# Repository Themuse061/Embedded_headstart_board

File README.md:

# Embedded_headstart_board

## How to use

> [!NOTE]
> Dear trainees, please note that this is the first version of this guide and it may contain errors. If you spot anything or something isn't working as expected, please contact [me](https://github.com/Fiedal) (if it comes to this readme or software) or [owner of this repo](https://github.com/Themuse061) (if it comes to hardware).

### Schematics

First of all, you are going to need software that allows you to read the schematics of the board. That's one of the most important skills for an embedded programmer. My main recommendation is installing **KiCad**, the EDA software in which this board was created. Another great alternative is [KiCanvas](https://kicanvas.org/), an online viewer for KiCad PCB layouts and schematics. It works great for simpler boards like this one, though KiCad is better for more complex projects.

### Altmode and Chainbus mode

MMS3 (the main board that this PCB connects to) has two modes: **Altmode** and **Chainbus mode**. What's the difference?

- **Chainbus mode:** This is the default mode. It lets you stack multiple hats (boards like this one) onto the MMS3 to build a tower (up to 8 boards). The tradeoff is that you only have SPI, I2C, and UART available on each hat. This means you cannot use direct hardware interrupts on peripherals located on the hat. However, you can still control simple peripherals using a GPIO expander. More details will be available in the upcoming MODUCAR and MMS3 documentation.

- **Altmode:** This mode is designed for specific use cases (like this headstart board). In Altmode, only a single hat can be connected to the MMS3, but you get access to a whole row of dedicated pins alongside the standard Chainbus interface. You can configure these free pins however you like: direct interrupts, SPI, USART, or ADC! Check the main schematic of this board to see the table showing how each pin can be assigned in Altmode.

*Note:* On this specific board, you don't need to manually switch modes – it was designed specifically to work in **Altmode**.

### Programming

There are several ways to program STM32 microcontrollers: using STM's official HAL (Hardware Abstraction Layer), writing bare-metal code, or using third-party libraries and OSes.

In KoNaR, we primarily use two approaches:
- [StmEpic](https://github.X-Lemon-X/StmEpic) – A library developed within KoNaR (used in Nomad) that acts as an abstraction layer over HAL, integrated with FreeRTOS.
- [Zephyr RTOS](https://docs.zephyrproject.org/latest/index.html) – An RTOS ecosystem used in Hefajstos (and currently being prepared for Nomad). Unlike lightweight RTOSes, Zephyr is a full ecosystem supporting multiple architectures, built-in connectivity stacks, Devicetree hardware description, and Kconfig build control.

We recommend starting with **HAL** first, as it is beginner-friendly and helps you understand what happens under the hood before moving to StmEpic or Zephyr.

#### HAL
Clone this [template repository](https://github.com/Fiedal/MMS-embedded-headstart-software-base). It already includes the base Chainbus pin definitions. All you need to do is configure the Altmode pins inside STM32CubeMX (`.ioc` file), generate the project code, and flash the board.

#### StmEpic
**TODO**

#### Zephyr
A template for Zephyr RTOS is currently under development. In the meantime, check out this [Zephyr tutorial video](https://www.youtube.com/watch?v=mTJ_vKlMS_4) and refer to the official [Zephyr Documentation](https://docs.zephyrproject.org/latest/index.html). You can also look at the existing [mms_board_definitions repository](https://github.com/KoNaR-Hefajstos/mms_board_definitions).

---

### Dictionary
- **uC / MCU:** Microcontroller Unit
- **GPIO:** General-Purpose Input/Output
- **Blinky:** A simple LED toggling program (the "Hello World" of embedded systems)
- **Debouncing:** Mechanical buttons bounce back and forth rapidly when pressed, causing false triggers. Debouncing (in hardware or software) filters out these quick oscillations to register only a single clean press.

---

### Project Ideas

Here are a few project suggestions to help you combine different hardware peripherals on the board. Try bringing up each peripheral individually first before building a full project!

- **Smart Blinky:** Use direct GPIOs to build a status blinky with multiple modes (e.g., fast blink, heartbeat pattern, slow blink). Change modes using a tactile button configured with external interrupts. *Watch out for button debouncing in your interrupt handler!*

- **Home Temperature & Humidity Station:** Read data from the DHT11 sensor and display the temperature or humidity on the 7-segment display. Use a push button to toggle between showing temperature and humidity.

- **Digital Spirit Level / Tilt Sensor:** Use the onboard sensor MPU-6500 to detect tilt. Display the current angle on the 7-segment display or light up specific LEDs on the board depending on whether it's tilted left or right.

- **Simon Says Game:** Use the GPIO Expander section to create a Simon Says memory game. The LEDs blink in a random sequence, and the user must repeat the sequence using the buttons. Add difficulty scaling with faster blinks or longer sequences!

> [!NOTE]
> If you're building one of these projects using HAL, try integrating FreeRTOS to get familiar with multi-tasking concepts. It's not mandatory right away, but understanding RTOS fundamentals will be essential for future KoNaR projects!

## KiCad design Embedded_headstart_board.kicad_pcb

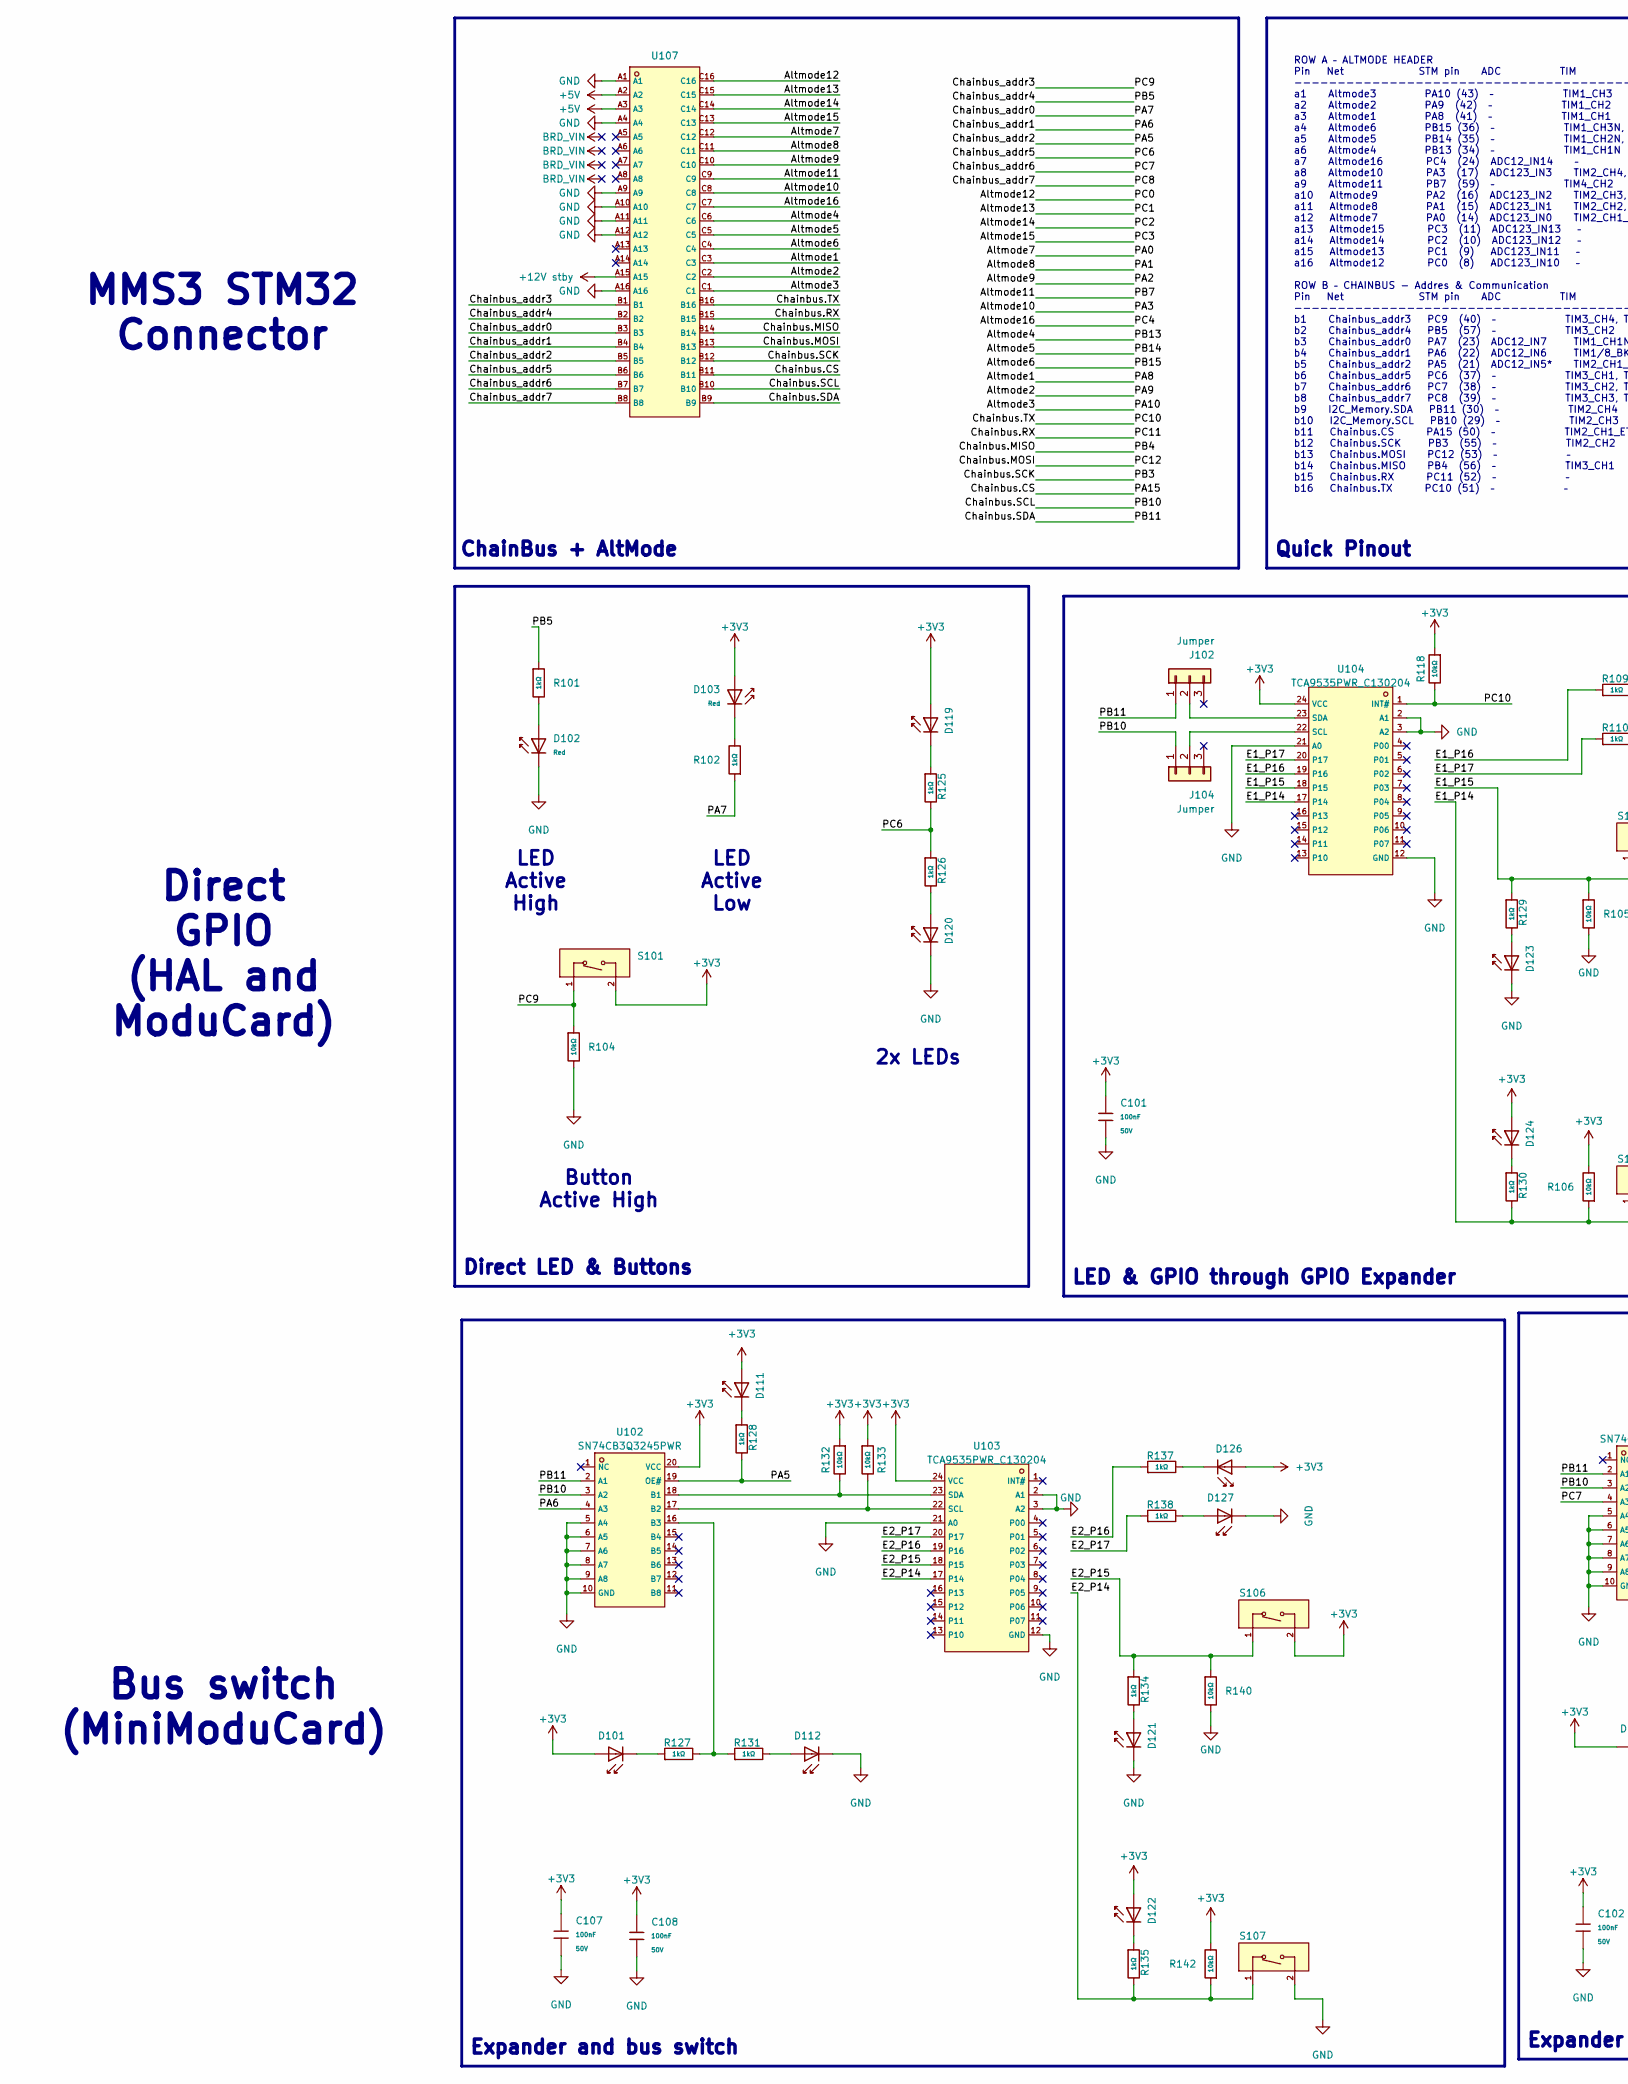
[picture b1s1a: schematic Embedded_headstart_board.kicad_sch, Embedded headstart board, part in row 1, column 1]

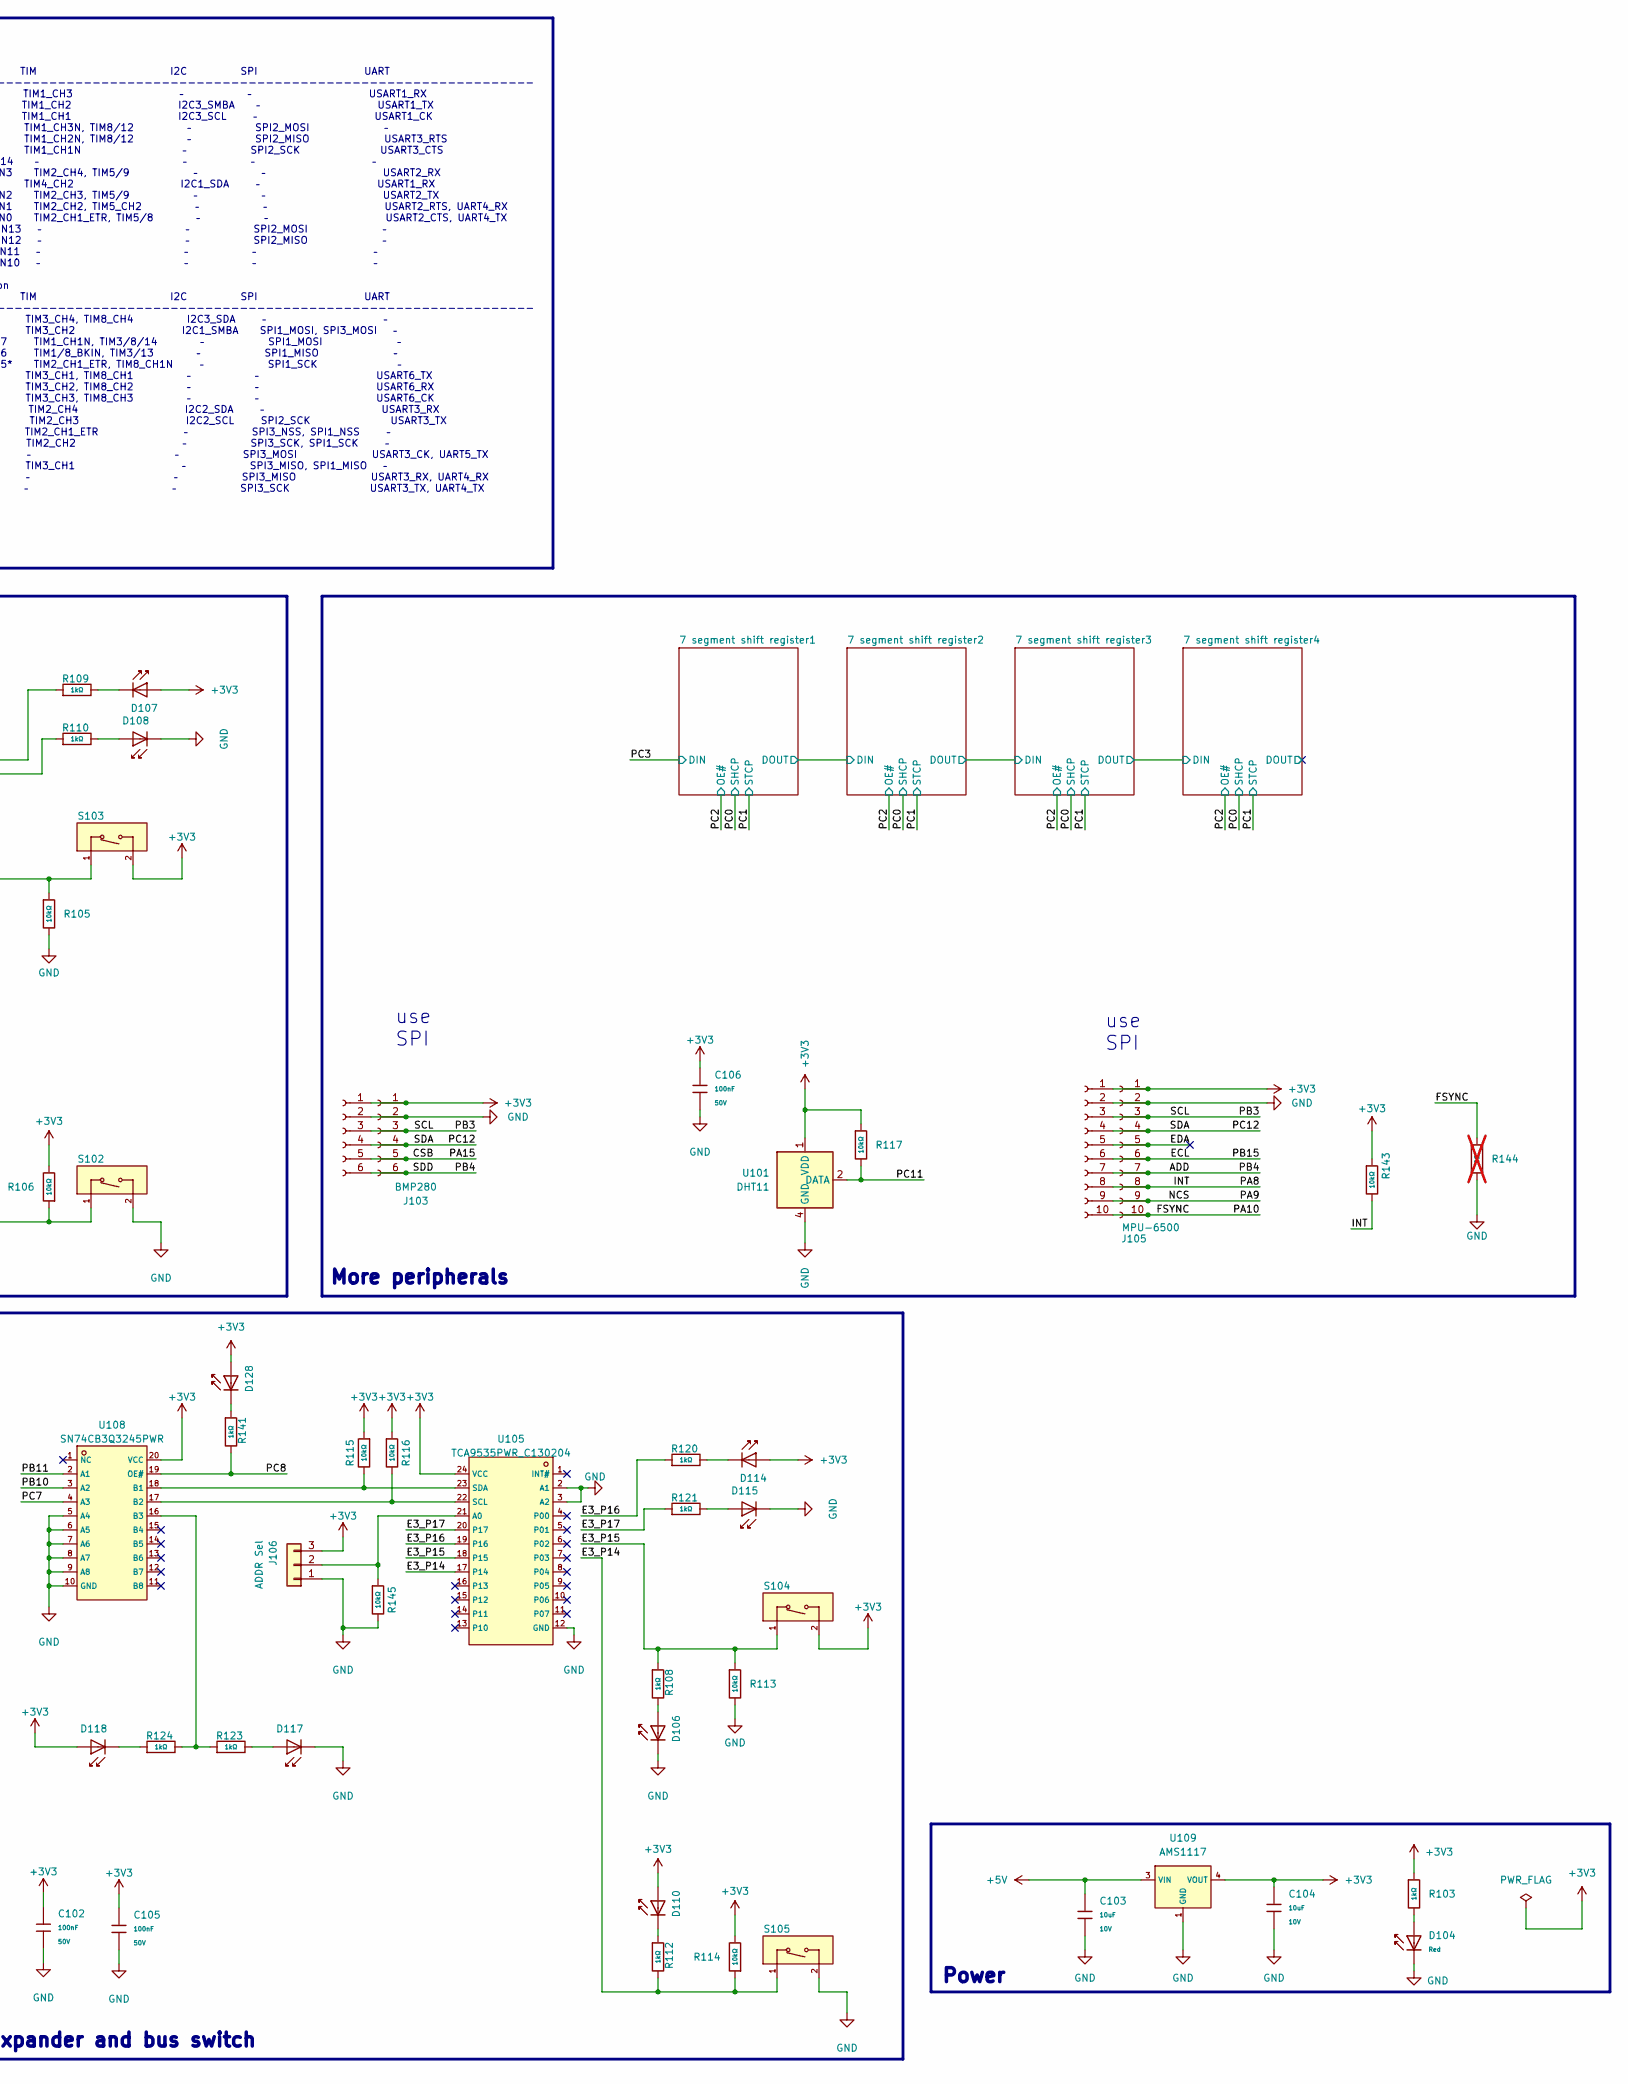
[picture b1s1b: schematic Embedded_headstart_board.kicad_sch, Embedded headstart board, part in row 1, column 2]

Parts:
C101, C102, C105, C106, C107, C108: 100nF; C_0603; Voltage Rated 50V; Tolerance ±10%; Part CC0603KRX7R9BB104; LCSC C14663
C103, C104: 10uF; C_0603; Voltage Rated 10V; Tolerance ±10%; Part CL10A106KP8NNNC; LCSC C19702
D101, D102, D103, D104, D107, D108, D111, D112, D114, D115, D117, D118, D119, D120, D126, D127, D128: Red; Multi_diode; Part KT-0603R; LCSC C2286
D106, D110, D121, D122, D123, D124: Red; D_0603; Part KT-0603R; LCSC C2286
J102, J104: Jumper; PinHeader_1x03_P2.54mm_Vertical
J103, J107: BMP280; PinHeader_1x06_P2.54mm_Vertical
J105, J108: MPU-6500; PinHeader_1x10_P2.54mm_Vertical
J106: ADDR Sel; PinHeader_1x03_P2.54mm_Vertical
R101, R102, R103, R108, R109, R110, R112, R120, R121, R123, R124, R125, R126, R127, R128, R129, R130, R131, R134, R135, R137, R138, R141: 1kΩ; R_0603; Overload Voltage (Max) 75V; Tolerance ±1%; Part 0603WAF1001T5E; LCSC C21190
R104, R105, R106, R113, R114, R115, R116, R117, R118, R132, R133, R140, R142, R143, R145: 10kΩ; R_0603; Overload Voltage (Max) 75V; Tolerance ±1%; Part 0603WAF1002T5E; LCSC C25804
R144: 0Ω; R_0603; Overload Voltage (Max) 75V; Tolerance ±1%; Part 0603WAF0000T5E; LCSC C21189; not fitted
S101, S102, S103, S104, S105, S106, S107: Tactile Button, 160gf; MultiSwitch; LCSC C55014078
U101: DHT11; Aosong_DHT11_5.5x12.0_P2.54mm
U102, U108: SN74CB3Q3245PWR; C470961_TSSOP-20_L6_5-W4_4-P0_65-LS6_4-BL; LCSC C470961
U103, U104, U105: TCA9535PWR_C130204; C130204_TSSOP-24_L7_8-W4_4-P0_65-LS6_4-BL; LCSC C22396388
U107: 9001-17481C00A_C5173377; C5173377_CONN-TH_9001-17481C00A; LCSC C5173377
U109: AMS1117; SOT-223-3_L6.5-W3.4-P2.30-LS7.0-BR; Output Voltage 3.3V; Dropout Voltage 1.3V@(800mA); Part AMS1117-3.3; LCSC C6186

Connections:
+3V3: C101.1, C102.1, C104.1, C105.1, C106.1, C107.1, C108.1, D101.2, D103.2, D107.2, D110.2, D111.2, D114.2, D118.2, D119.2, D122.2, D124.2, D126.2, D128.2, J103.1, J105.1, J106.3, J107.1, J108.1, R103.1, R106.2, R114.2, R115.1, R116.1, R117.1, R118.1, R132.1, R133.1, R142.2, R143.1, S101.2 (B), S103.2 (B), S104.2 (B), S106.2 (B), U101.1 (VDD), U102.20 (VCC), U103.24 (VCC), U104.24 (VCC), U105.24 (VCC), U108.20 (VCC), U109.2 (VOUT), U109.4 (VOUT); also elsewhere on the board
+5V: C103.1, U107.A2, U107.A3, U109.3 (VIN)
+12V stby: U107.A15
/ADD: J103.6, J105.7, J107.6, J108.7, U107.B14
/Altmode1: J105.8, J108.8, R143.2, U107.C3
/Altmode2: J105.9, J108.9, U107.C2
/Altmode3: J105.10, J108.10, R144.1, U107.C1
/Altmode4: U107.C6
/Altmode5: U107.C5
/Altmode6: J105.6, J108.6, U107.C4
/Altmode7: U107.C12
/Altmode8: U107.C11
/Altmode9: U107.C10
/Altmode10: U107.C8
/Altmode11: U107.C9
/Altmode12: U107.C16; also elsewhere on the board
/Altmode13: U107.C15; also elsewhere on the board
/Altmode14: U107.C14; also elsewhere on the board
/Altmode15: U107.C13; also elsewhere on the board
/Altmode16: U107.C7
/CSB: J103.5, J107.5, U107.B11
/Chainbus.MOSI: J103.4, J105.4, J107.4, J108.4, U107.B13
/Chainbus.RX: R117.2, U101.2 (DATA), U107.B15
/Chainbus.SCK: J103.3, J105.3, J107.3, J108.3, U107.B12
/Chainbus.SCL: J104.1, U102.3 (A2), U107.B10, U108.3 (A2)
/Chainbus.SDA: J102.1, U102.2 (A1), U107.B9, U108.2 (A1)
/Chainbus.TX: R118.2, U104.1 (INT#), U107.B16
/Chainbus_addr0: R102.1, U107.B3
/Chainbus_addr1: U102.4 (A3), U107.B4
/Chainbus_addr2: R128.2, U102.19 (OE#), U107.B5
/Chainbus_addr3: R104.1, S101.1 (A), U107.B1
/Chainbus_addr4: R101.1, U107.B2
/Chainbus_addr5: R125.2, R126.1, U107.B6
/Chainbus_addr6: U107.B7, U108.4 (A3)
/Chainbus_addr7: R141.2, U107.B8, U108.19 (OE#)
/E1_P14: R106.1, R130.2, S102.1 (A), U104.17 (P14)
/E1_P15: R105.1, R129.1, S103.1 (A), U104.18 (P15)
/E1_P16: R109.1, U104.19 (P16)
/E1_P17: R110.1, U104.20 (P17)
/E2_P14: R135.2, R142.1, S107.1 (A), U103.17 (P14)
/E2_P15: R134.1, R140.1, S106.1 (A), U103.18 (P15)
/E2_P16: R137.1, U103.19 (P16)
/E2_P17: R138.1, U103.20 (P17)
/E3_P14: R112.2, R114.1, S105.1 (A), U105.17 (P14)
/E3_P15: R108.1, R113.1, S104.1 (A), U105.18 (P15)
/E3_P16: R120.1, U105.19 (P16)
/E3_P17: R121.1, U105.20 (P17)
/EDA: J105.5, J108.5
GND: C101.2, C102.2, C103.2, C104.2, C105.2, C106.2, C107.2, C108.2, D102.1, D104.1, D106.1, D108.1, D112.1, D115.1, D117.1, D120.1, D121.1, D123.1, D127.1, J103.2, J105.2, J106.1, J107.2, J108.2, R104.2, R105.2, R113.2, R140.2, R144.2, R145.2, S102.2 (B), S105.2 (B), S107.2 (B), U101.4 (GND), U102.5 (A4), U102.6 (A5), U102.7 (A6), U102.8 (A7), U102.9 (A8), U102.10 (GND), U103.2 (A1), U103.3 (A2), U103.12 (GND), U103.21 (A0), U104.2 (A1), U104.3 (A2), U104.12 (GND), U104.21 (A0), U105.2 (A1), U105.3 (A2), U105.12 (GND), U107.A1, U107.A4, U107.A9, U107.A10, U107.A11, U107.A12, U107.A16, U108.5 (A4), U108.6 (A5), U108.7 (A6), U108.8 (A7), U108.9 (A8), U108.10 (GND), U109.1 (GND); also elsewhere on the board
unnamed: D101.1, R127.1
unnamed: D102.2, R101.2
unnamed: D103.1, R102.2
unnamed: D104.2, R103.2
unnamed: D106.2, R108.2
unnamed: D107.1, R109.2
unnamed: D108.2, R110.2
unnamed: D110.1, R112.1
unnamed: D111.1, R128.1
unnamed: D112.2, R131.2
unnamed: D114.1, R120.2
unnamed: D115.2, R121.2
unnamed: D117.2, R123.2
unnamed: D118.1, R124.1
unnamed: D119.1, R125.1
unnamed: D120.2, R126.2
unnamed: D121.2, R134.2
unnamed: D122.1, R135.1
unnamed: D123.2, R129.2
unnamed: D124.1, R130.1
unnamed: D126.1, R137.2
unnamed: D127.2, R138.2
unnamed: D128.1, R141.1
unnamed: J102.2, U104.23 (SDA)
unnamed: J104.2, U104.22 (SCL)
unnamed: J106.2, R145.1, U105.21 (A0)
unnamed: R132.2, U102.18 (B1), U103.23 (SDA)
unnamed: R133.2, U102.17 (B2), U103.22 (SCL)
unnamed: R127.2, R131.1, U102.16 (B3)
unnamed: R116.2, U105.22 (SCL), U108.17 (B2)
unnamed: R115.2, U105.23 (SDA), U108.18 (B1)
unnamed: R123.1, R124.2, U108.16 (B3)

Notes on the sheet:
use SPI
LED Active Low
Power
LED & GPIO through GPIO Expander
Direct GPIO (HAL and ModuCard)
2x LEDs
LED Active High
Direct LED & Buttons
Button Active High
ChainBus + AltMode
ROW A – ALTMODE HEADER Pin Net STM pin ADC TIM I2C SPI UART ------------------------------------------------------------------------------------------ a1 Altmode3 PA10 (43) – TIM1_CH3 – – USART1_RX a2 Altmode2 PA9 (42) – TIM1_CH2 I2C3_SMBA – USART1_TX a3 Altmode1 PA8 (41) – TIM1_CH1 I2C3_SCL – USAR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
Expander and bus switch
Quick Pinout
More peripherals
Bus switch (MiniModuCard)
MMS3 STM32 Connector

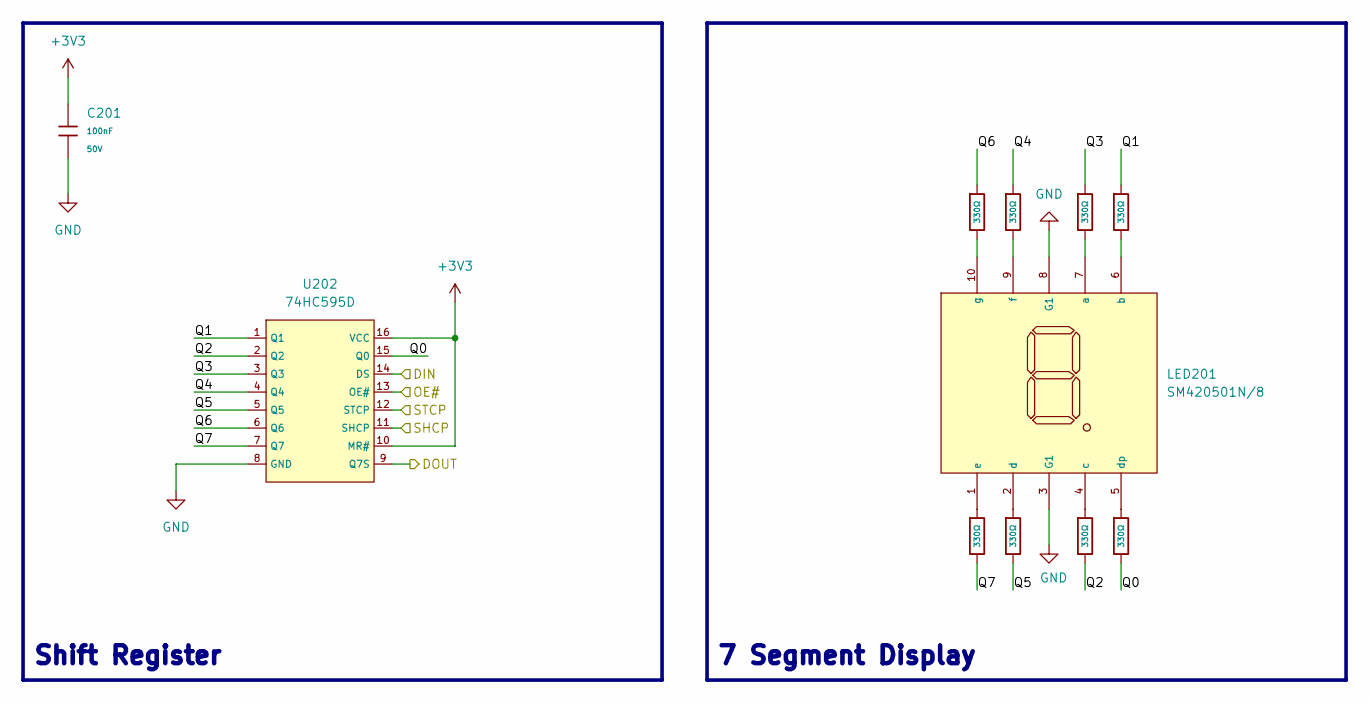
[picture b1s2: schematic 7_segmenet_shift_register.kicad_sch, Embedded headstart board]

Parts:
C201: 100nF; C_0603; Voltage Rated 50V; Tolerance ±10%; Part CC0603KRX7R9BB104; LCSC C14663
LED201: SM420501N/8; C252201_LED-SEG-TH_10P-L12_7-W19_0-P2_54-S15_24-BL; LCSC C252201
R201, R202, R203, R204, R205, R206, R207, R208: 330Ω; R_0603; Overload Voltage (Max) 75V; Tolerance ±1%; Part 0603WAF3300T5E; LCSC C23138
U202: 74HC595D; SOIC-16_L9.9-W3.9-P1.27-LS6.0-BL; Supply Voltage 2V~6V; Part 74HC595D,118; LCSC C5947

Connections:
+3V3: C201.1, U202.10 (MR#), U202.16 (VCC); also elsewhere on the board
/7 segment shift register1/DOUT: U202.9 (Q7S); also elsewhere on the board
/7 segment shift register1/Q0: R208.2, U202.15 (Q0)
/7 segment shift register1/Q1: R207.1, U202.1 (Q1)
/7 segment shift register1/Q2: R206.2, U202.2 (Q2)
/7 segment shift register1/Q3: R205.1, U202.3 (Q3)
/7 segment shift register1/Q4: R203.1, U202.4 (Q4)
/7 segment shift register1/Q5: R204.2, U202.5 (Q5)
/7 segment shift register1/Q6: R201.1, U202.6 (Q6)
/7 segment shift register1/Q7: R202.2, U202.7 (Q7)
/Altmode12: U202.11 (SHCP); also elsewhere on the board
/Altmode13: U202.12 (STCP); also elsewhere on the board
/Altmode14: U202.13 (OE#); also elsewhere on the board
/Altmode15: U202.14 (DS); also elsewhere on the board
GND: C201.2, LED201.3 (G1), LED201.8 (G1), U202.8 (GND); also elsewhere on the board
unnamed: LED201.7 (a), R205.2
unnamed: LED201.6 (b), R207.2
unnamed: LED201.4 (c), R206.1
unnamed: LED201.2 (d), R204.1
unnamed: LED201.5 (dp), R208.1
unnamed: LED201.1 (e), R202.1
unnamed: LED201.9 (f), R203.2
unnamed: LED201.10 (g), R201.2

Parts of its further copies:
C301, C401, C501: 100nF; C_0603; Voltage Rated 50V; Tolerance ±10%; Part CC0603KRX7R9BB104; LCSC C14663
LED301, LED401, LED501: SM420501N/8; C252201_LED-SEG-TH_10P-L12_7-W19_0-P2_54-S15_24-BL; LCSC C252201
R301, R302, R303, R304, R305, R306, R307, R308, R401, R402, R403, R404, R405, R406, R407, R408, R501, R502, R503, R504, R505, R506, R507, R508: 330Ω; R_0603; Overload Voltage (Max) 75V; Tolerance ±1%; Part 0603WAF3300T5E; LCSC C23138
U301, U401, U501: 74HC595D; SOIC-16_L9.9-W3.9-P1.27-LS6.0-BL; Supply Voltage 2V~6V; Part 74HC595D,118; LCSC C5947

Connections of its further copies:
+3V3: C301.1, C401.1, C501.1, U301.10 (MR#), U301.16 (VCC), U401.10 (MR#), U401.16 (VCC), U501.10 (MR#), U501.16 (VCC); also elsewhere on the board
/7 segment shift register1/DOUT: U301.14 (DS); also elsewhere on the board
/7 segment shift register2/DOUT: U301.9 (Q7S), U401.14 (DS)
/7 segment shift register2/Q0: R308.2, U301.15 (Q0)
/7 segment shift register2/Q1: R307.1, U301.1 (Q1)
/7 segment shift register2/Q2: R306.2, U301.2 (Q2)
/7 segment shift register2/Q3: R305.1, U301.3 (Q3)
/7 segment shift register2/Q4: R303.1, U301.4 (Q4)
/7 segment shift register2/Q5: R304.2, U301.5 (Q5)
/7 segment shift register2/Q6: R301.1, U301.6 (Q6)
/7 segment shift register2/Q7: R302.2, U301.7 (Q7)
/7 segment shift register3/DOUT: U401.9 (Q7S), U501.14 (DS)
/7 segment shift register3/Q0: R408.2, U401.15 (Q0)
/7 segment shift register3/Q1: R407.1, U401.1 (Q1)
/7 segment shift register3/Q2: R406.2, U401.2 (Q2)
/7 segment shift register3/Q3: R405.1, U401.3 (Q3)
/7 segment shift register3/Q4: R403.1, U401.4 (Q4)
/7 segment shift register3/Q5: R404.2, U401.5 (Q5)
/7 segment shift register3/Q6: R401.1, U401.6 (Q6)
/7 segment shift register3/Q7: R402.2, U401.7 (Q7)
/7 segment shift register4/DOUT: U501.9 (Q7S)
/7 segment shift register4/Q0: R508.2, U501.15 (Q0)
/7 segment shift register4/Q1: R507.1, U501.1 (Q1)
/7 segment shift register4/Q2: R506.2, U501.2 (Q2)
/7 segment shift register4/Q3: R505.1, U501.3 (Q3)
/7 segment shift register4/Q4: R503.1, U501.4 (Q4)
/7 segment shift register4/Q5: R504.2, U501.5 (Q5)
/7 segment shift register4/Q6: R501.1, U501.6 (Q6)
/7 segment shift register4/Q7: R502.2, U501.7 (Q7)
/Altmode12: U301.11 (SHCP), U401.11 (SHCP), U501.11 (SHCP); also elsewhere on the board
/Altmode13: U301.12 (STCP), U401.12 (STCP), U501.12 (STCP); also elsewhere on the board
/Altmode14: U301.13 (OE#), U401.13 (OE#), U501.13 (OE#); also elsewhere on the board
GND: C301.2, C401.2, C501.2, LED301.3 (G1), LED301.8 (G1), LED401.3 (G1), LED401.8 (G1), LED501.3 (G1), LED501.8 (G1), U301.8 (GND), U401.8 (GND), U501.8 (GND); also elsewhere on the board
unnamed: LED301.7 (a), R305.2
unnamed: LED301.6 (b), R307.2
unnamed: LED301.4 (c), R306.1
unnamed: LED301.2 (d), R304.1
unnamed: LED301.5 (dp), R308.1
unnamed: LED301.1 (e), R302.1
unnamed: LED301.9 (f), R303.2
unnamed: LED301.10 (g), R301.2
unnamed: LED401.7 (a), R405.2
unnamed: LED401.6 (b), R407.2
unnamed: LED401.4 (c), R406.1
unnamed: LED401.2 (d), R404.1
unnamed: LED401.5 (dp), R408.1
unnamed: LED401.1 (e), R402.1
unnamed: LED401.9 (f), R403.2
unnamed: LED401.10 (g), R401.2
unnamed: LED501.7 (a), R505.2
unnamed: LED501.6 (b), R507.2
unnamed: LED501.4 (c), R506.1
unnamed: LED501.2 (d), R504.1
unnamed: LED501.5 (dp), R508.1
unnamed: LED501.1 (e), R502.1
unnamed: LED501.9 (f), R503.2
unnamed: LED501.10 (g), R501.2

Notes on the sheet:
Shift Register
7 Segment Display

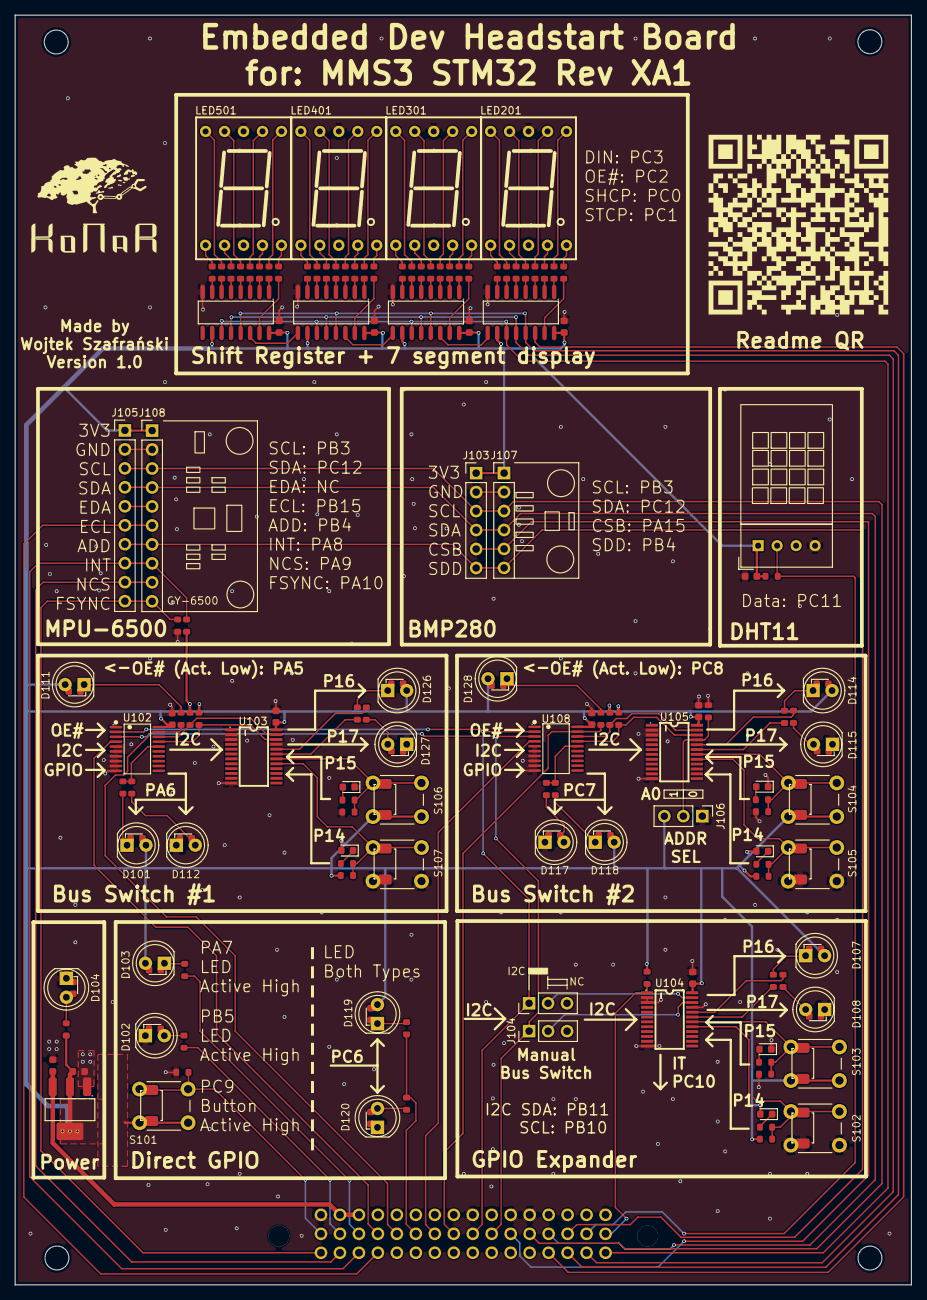
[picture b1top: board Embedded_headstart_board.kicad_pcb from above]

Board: 2 copper layers, 120.0 x 170.0 mm, 137 parts (1 on the bottom side), 139 nets.

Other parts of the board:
konar1: LOGO; konar
